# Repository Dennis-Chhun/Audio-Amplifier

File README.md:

# Audio-Amplifier
Dual channel, low-impedance amplifier that will strengthen low power, inaudible electronic audio signals.

  - Utilized bridge rectifiers and linear voltage regulators to power two AD797N Integrated Circuits.

  - Two AD797 Integrated Circuits were used to create a left and right channel for noise minimization.

  - Eagle for schematic capture and PCB layout.

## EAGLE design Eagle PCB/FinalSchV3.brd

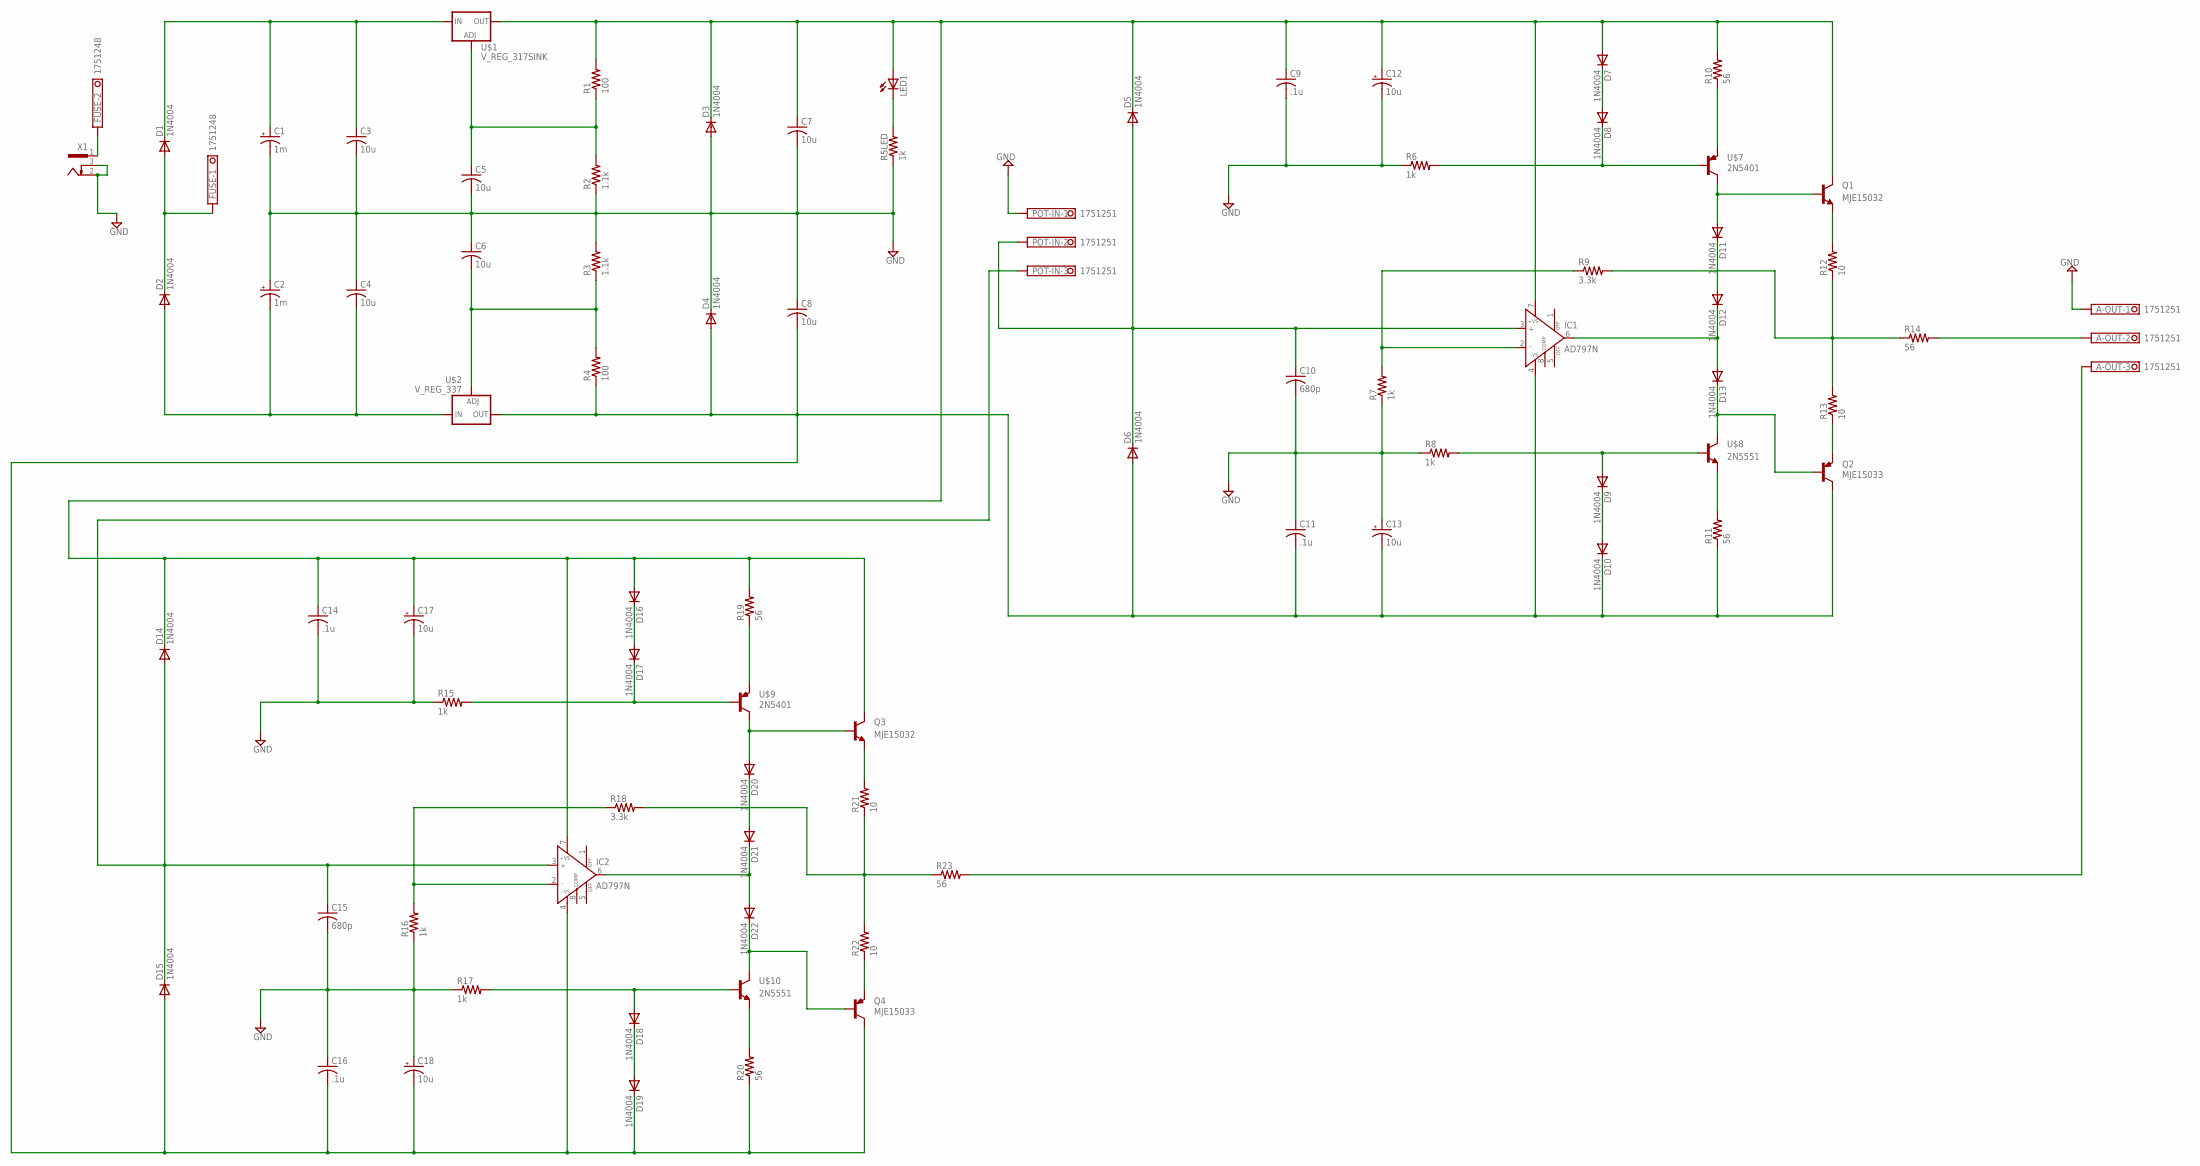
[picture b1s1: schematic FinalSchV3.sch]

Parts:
A-OUT: 1751251
C1, C2: 1m; E7,5-16
C3, C4, C5, C6, C7, C8: 10u; C025-025X050
C9, C11, C14, C16: .1u; C025-024X044
C10, C15: 680p; C025-024X044
C12, C13, C17, C18: 10u; E2-5
D1, D2, D3, D4, D5, D6, D7, D8, D9, D10, D11, D12, D13, D14, D15, D16, D17, D18, D19, D20, D21, D22: 1N4004; DO41-10
FUSE: 1751248
IC1, IC2: AD797N; DIL08
LED1: LED5MM
POT-IN: 1751251
Q1, Q3: MJE15032; TO220V
Q2, Q4: MJE15033; TO220V
R1, R4: 100; 0207/7
R2, R3: 1.1k; 0207/7
R5LED, R6, R7, R8, R15, R16, R17: 1k; 0207/7
R9, R18: 3.3k; 0207/7
R10, R11, R14, R19, R20, R23: 56; 0207/7
R12, R13, R21, R22: 10; 0207/7
U$1: V_REG_317SINK; TO220-ADJ
U$2: V_REG_337; TO220-ADJ-NEG
U$7, U$9: 2N5401
U$8, U$10: 2N5551
X1: 733980-62

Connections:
GND: A-OUT.1, C9.2, C10.2, C11.1, C12.-, C13.+, C14.2, C15.2, C16.1, C17.-, C18.+, POT-IN.1, R6.1, R7.1, R8.1, R15.1, R16.1, R17.1
GPWR: C1.-, C2.+, C3.2, C4.1, C5.2, C6.1, C7.2, C8.1, D3.A, D4.C, R2.1, R3.2, R5LED.1, X1.2, X1.3
unnamed: C1.+, C3.1, D1.C, U$1.IN
unnamed: D1.A, D2.C, FUSE.1
unnamed: C2.-, C4.2, D2.A, U$2.IN
unnamed: D7.C, D8.A
unnamed: A-OUT.2, R14.2
unnamed: D8.C, R6.2, U$7.B
unnamed: A-OUT.3, R23.2
unnamed: FUSE.2, X1.1
unnamed: C6.2, R3.1, R4.2, U$2.ADJ
unnamed: D11.A, Q1.1 (B), U$7.C
unnamed: C5.1, R1.1, R2.2, U$1.ADJ
unnamed: D16.C, D17.A
unnamed: D11.C, D12.A
unnamed: D12.C, D13.A, IC1.6 (OUT)
unnamed: LED1.K (C), R5LED.2
unnamed: C10.1, D5.A, D6.C, IC1.3 (IN+), POT-IN.2
unnamed: D13.C, Q2.1 (B), U$8.C
unnamed: R11.2, U$8.E
unnamed: IC1.2 (IN-), R7.2, R9.1
unnamed: D17.C, R15.2, U$9.B
unnamed: D20.A, Q3.1 (B), U$9.C
unnamed: D9.A, R8.2, U$8.B
unnamed: D9.C, D10.A
unnamed: D20.C, D21.A
unnamed: Q1.3 (E), R12.2
unnamed: R9.2, R12.1, R13.2, R14.1
unnamed: Q2.3 (E), R13.1
unnamed: D21.C, D22.A, IC2.6 (OUT)
unnamed: D22.C, Q4.1 (B), U$10.C
unnamed: R20.2, U$10.E
unnamed: IC2.2 (IN-), R16.2, R18.1
unnamed: D18.A, R17.2, U$10.B
unnamed: D18.C, D19.A
unnamed: C15.1, D14.A, D15.C, IC2.3 (IN+), POT-IN.3
unnamed: Q3.3 (E), R21.2
unnamed: R18.2, R21.1, R22.2, R23.1
unnamed: Q4.3 (E), R22.1
unnamed: C8.2, C11.2, C13.-, C16.2, C18.-, D4.A, D6.A, D10.C, D15.A, D19.C, IC1.4 (-VS), IC2.4 (-VS), Q2.2 (C), Q4.2 (C), R4.1, R11.1, R20.1, U$2.OUT
Q1: R10.1, U$7.E
Q3: C7.1, C9.1, C12.+, C14.1, C17.+, D3.C, D5.C, D7.A, D14.C, D16.A, IC1.7 (+VS), IC2.7 (+VS), LED1.A, Q1.2 (C), Q3.2 (C), R1.2, R10.2, R19.2, U$1.OUT
Q4: R19.1, U$9.E

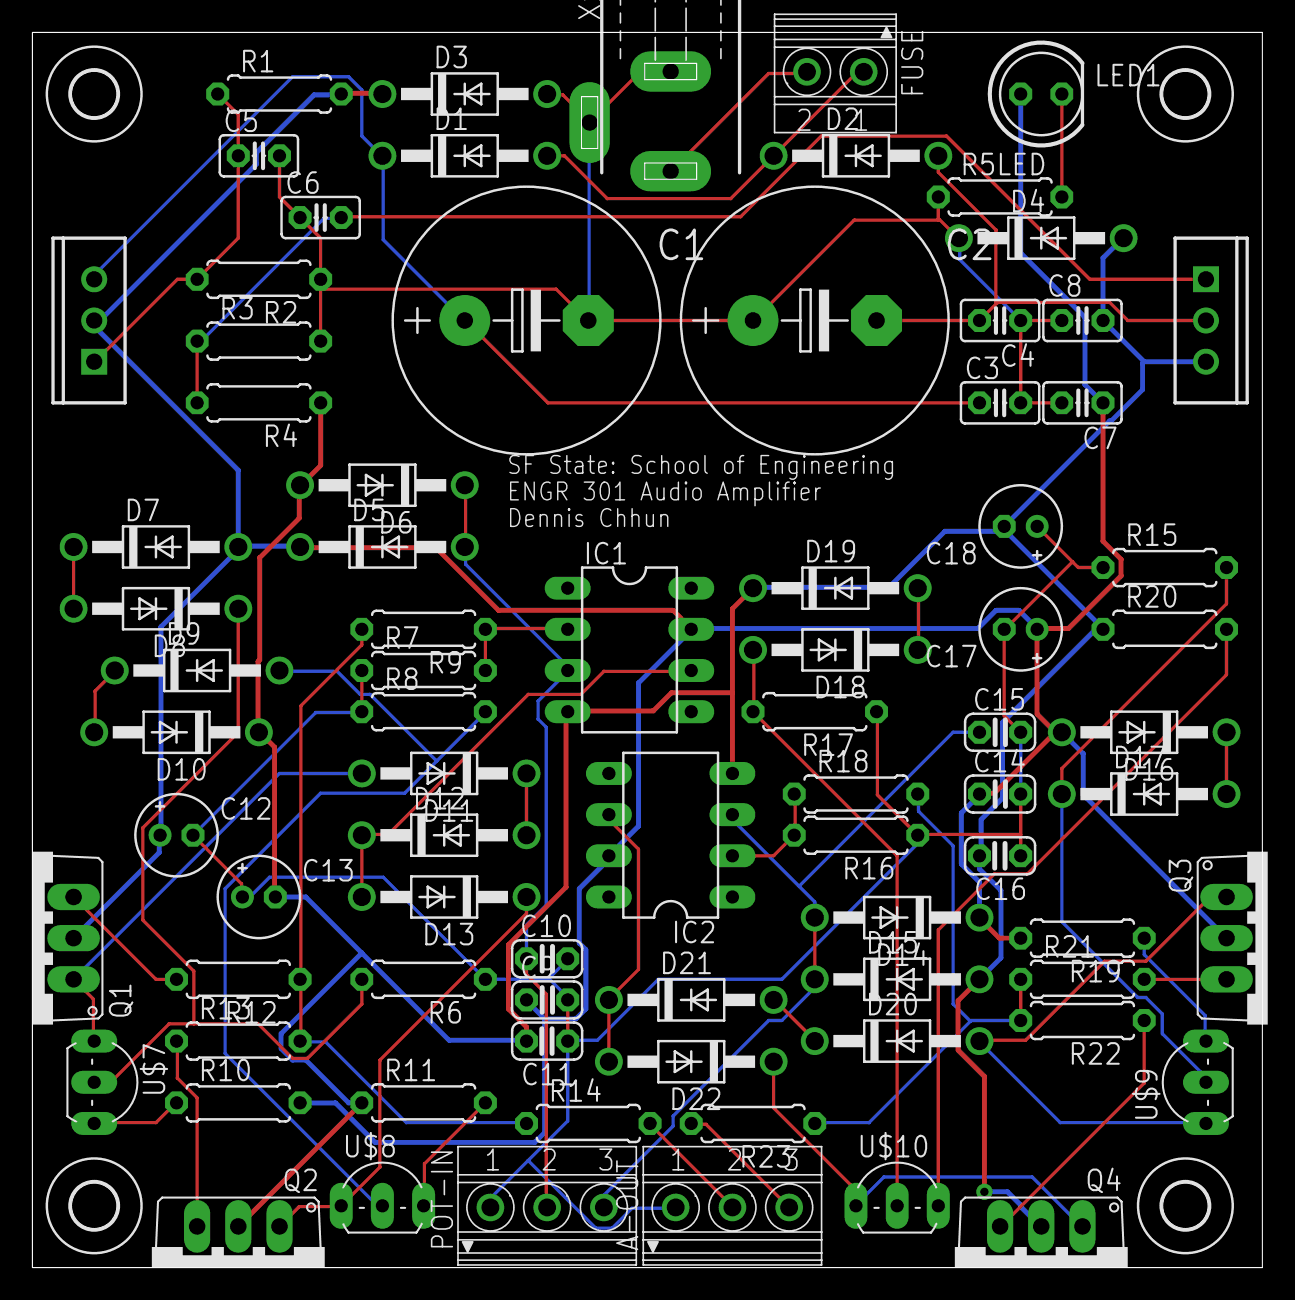
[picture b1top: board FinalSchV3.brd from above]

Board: 2 copper layers, 75.9 x 76.2 mm, 84 parts (0 on the bottom side), 43 nets.

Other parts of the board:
U$3, U$4, U$5, U$6: 2,8

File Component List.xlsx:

|  | Note | $$$/qty | Quantity | Website
 | Capacitor
 | 680 pF | non-polarized | 0.28999999999999998 | 2 | http://www.digikey.com/product-detail/en/vishay-bc-component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
 | 0.1 uF (100 nF) | non-polarized | 0.21 | 4 | http://www.digikey.com/product-detail/en/vishay-bc-component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
 | 10 uF | non-polarized | 1.06 | 6 | http://www.digikey.com/product-detail/en/tdk-corporation/FK2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
 | 10 uF | polarized | 0.26 | 4 | http://www.digikey.com/product-detail/en/nichicon/UMA0J100MC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
 | 1000 uF (1 mF) | polarized | 0.44 | 2 | http://www.digikey.com/product-detail/en/nichicon/UVR1E102MP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
 | Resistor
 | 10 | 1/4 Watt | 0.1 | 4 | http://www.digikey.com/product-detail/en/stackpole-electroni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
 | 56 | 1/4 Watt | 0.1 | 4 | http://www.digikey.com/product-detail/en/yageo/CFR-25JB-52-5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
 | 56 | 1 Watt | 0.15 | 2 | http://www.digikey.com/product-detail/en/yageo/FMP100JR-52-5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
 | 100 | 1/4 Watt | 0.1 | 2 | http://www.digikey.com/product-detail/en/stackpole-electroni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
 | 1k | 1/4 Watt | 0.1 | 7 | http://www.digikey.com/product-detail/en/stackpole-electroni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
 | 1.1k | 1/4 Watt | 0.1 | 2 | http://www.digikey.com/product-detail/en/yageo/CFR-25JB-52-1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
 | 3.3k | 1/4 Watt | 0.1 | 2 | http://www.digikey.com/product-detail/en/stackpole-electroni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
 | 10k | dual-gang pot | 4.79 | 1 | http://www.digikey.com/product-detail/en/te-connectivity-amp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
 | Diode
 | 1N4004 |  | 0.13 | 4 | http://www.digikey.com/product-detail/en/diodes-incorporated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
 | 1N40148 |  | 0.1 | 18 | http://www.digikey.com/product-detail/en/micro-commercial-co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
 | BJT
 | 2N5401 |  | 0.41 | 2 | http://www.digikey.com/product-detail/en/central-semiconduct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
 | 2N5551 |  | 0.2 | 2 | http://www.digikey.com/product-detail/en/fairchild-semicondu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
 | MJE15032 |  | 1.5 | 2 | http://www.digikey.com/product-detail/en/on-semiconductor/MJ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
 | MJE15033 |  | 1.5 | 2 | http://www.digikey.com/product-detail/en/on-semiconductor/MJ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
 | Voltage Regulator
 | LM317 | positive | 0.53 | 1 | http://www.digikey.com/product-detail/en/on-semiconductor/LM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
 | LM337 | negative | 0.87 | 1 | http://www.digikey.com/product-detail/en/on-semiconductor/LM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
 | Opamp
 | OP275 | dual-opamp | 2.79 | 1 | http://www.digikey.com/product-search/en/integrated-circuits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
 | Power Indicator
 | LED |  | 0.23 | 1 | http://www.digikey.com/product-detail/en/cree-inc/C566C-RFS-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
 | Fuse
 | 1A | 5.2mm x 20mm | 0.36 | 1 | http://www.digikey.com/product-detail/en/littelfuse-inc/0217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
 | I/O Pins
 | Power Jack |  | 0.93 | 1 | http://www.digikey.com/product-detail/en/cui-inc/PJ-002A/CP-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
 | Fuse Holder |  | 1.32 | 1 | http://www.digikey.com/product-detail/en/mpd-memory-protecti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
 | 3.5mm Audio Jack |  | 1.95 | 2 | http://www.digikey.com/product-detail/en/cui-inc/SJ1-3534/CP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
 | IC Socket | 8-pin | 0.19 | 1 | http://www.digikey.com/product-detail/en/amphenol-fci/DILB8P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
 | Optional
 | Terminal Block | 2-pin | 0.43 | 1 | http://www.digikey.com/product-detail/en/te-connectivity-amp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
 | Terminal Block | 3-pin | 0.61 | 2 | http://www.digikey.com/product-detail/en/phoenix-contact/198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
 | AD797N | single-opamp | 10.38 | 2 | http://www.digikey.com/product-search/en/integrated-circuits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 | The opamp and IC socket are used to replace the op275.
 | IC Socket | 8-pin | 0.19 | 2 | http://www.digikey.com/product-detail/en/amphenol-fci/DILB8P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
